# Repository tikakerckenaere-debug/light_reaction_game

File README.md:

# light_reaction_game
<h3>A game with buttons and lights!</h3>
<p><b>I present to you</b></p>
<p>A light reaction game where if a light shines you click the button as fast as you can.</p>

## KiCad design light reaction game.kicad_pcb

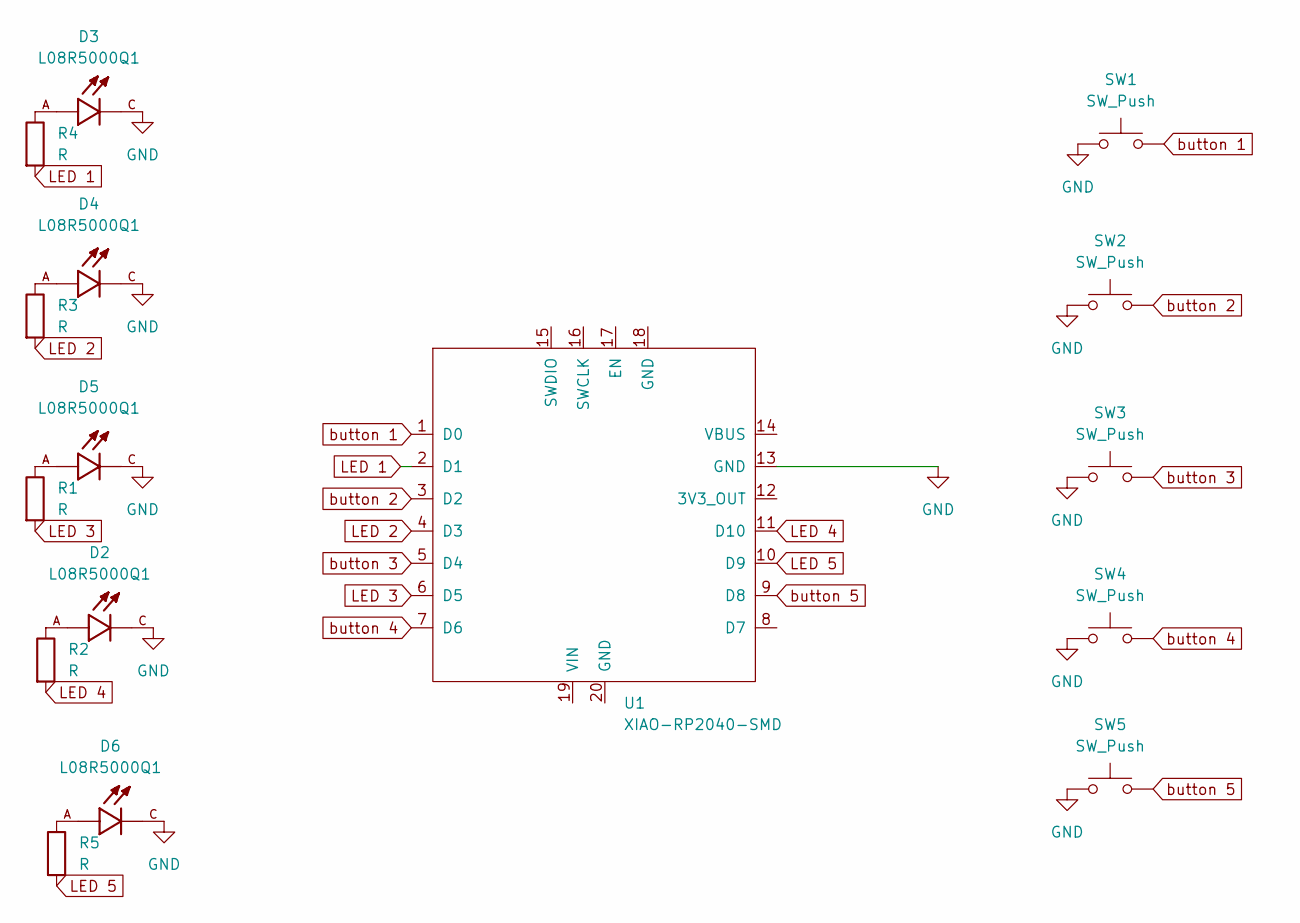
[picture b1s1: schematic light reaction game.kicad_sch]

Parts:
D2, D3, D4, D5, D6: L08R5000Q1; LEDRD254W57D500H1070; PARTREV NA
R1, R2, R3, R4, R5: R; R_Axial_DIN0204_L3.6mm_D1.6mm_P5.08mm_Horizontal
SW1, SW2, SW3, SW4, SW5: SW_Push; SW_Cherry_MX_1.00u_PCB
U1: XIAO-RP2040-SMD

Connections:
GND: D2.C, D3.C, D4.C, D5.C, D6.C, SW1.1, SW2.1, SW3.1, SW4.1, SW5.1, U1.13 (GND)
LED 1: R4.2, U1.2 (D1)
LED 2: R3.2, U1.4 (D3)
LED 3: R1.2, U1.6 (D5)
LED 4: R2.2, U1.11 (D10)
LED 5: R5.2, U1.10 (D9)
unnamed: D2.A, R2.1
unnamed: D3.A, R4.1
unnamed: D4.A, R3.1
unnamed: D5.A, R1.1
unnamed: D6.A, R5.1
button 1: SW1.2, U1.1 (D0)
button 2: SW2.2, U1.3 (D2)
button 3: SW3.2, U1.5 (D4)
button 4: SW4.2, U1.7 (D6)
button 5: SW5.2, U1.9 (D8)

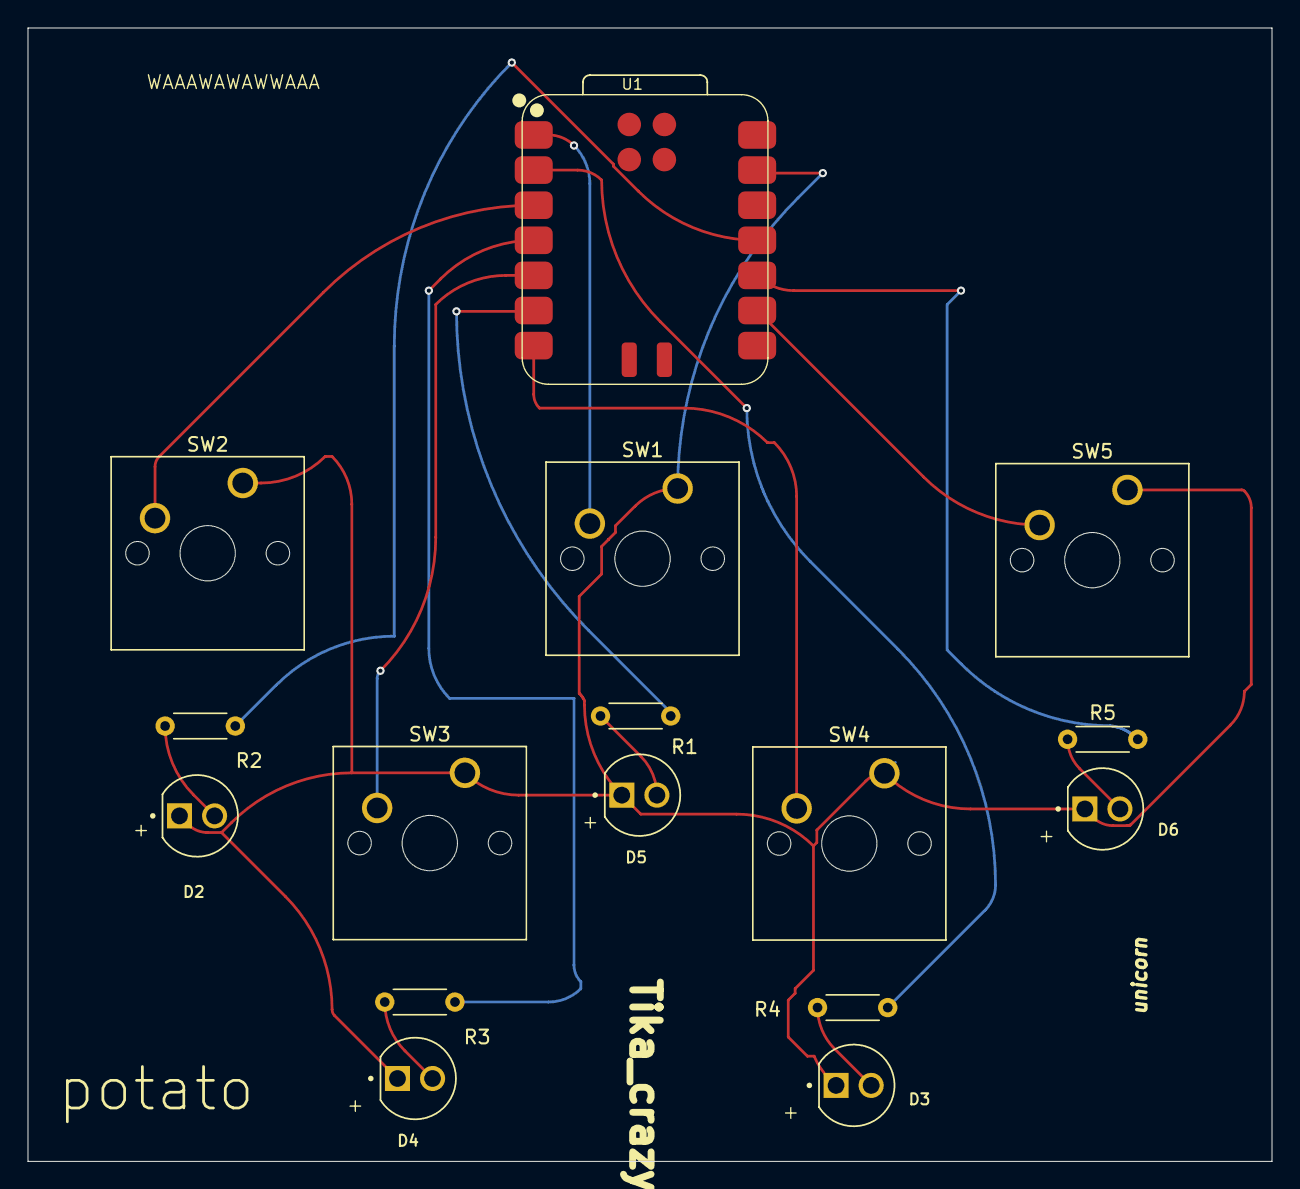
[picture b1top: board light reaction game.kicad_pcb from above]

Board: 2 copper layers, 90.0 x 82.0 mm, 16 parts (0 on the bottom side), 16 nets.
